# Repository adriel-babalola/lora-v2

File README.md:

# lora-v2

This is lora board version 2

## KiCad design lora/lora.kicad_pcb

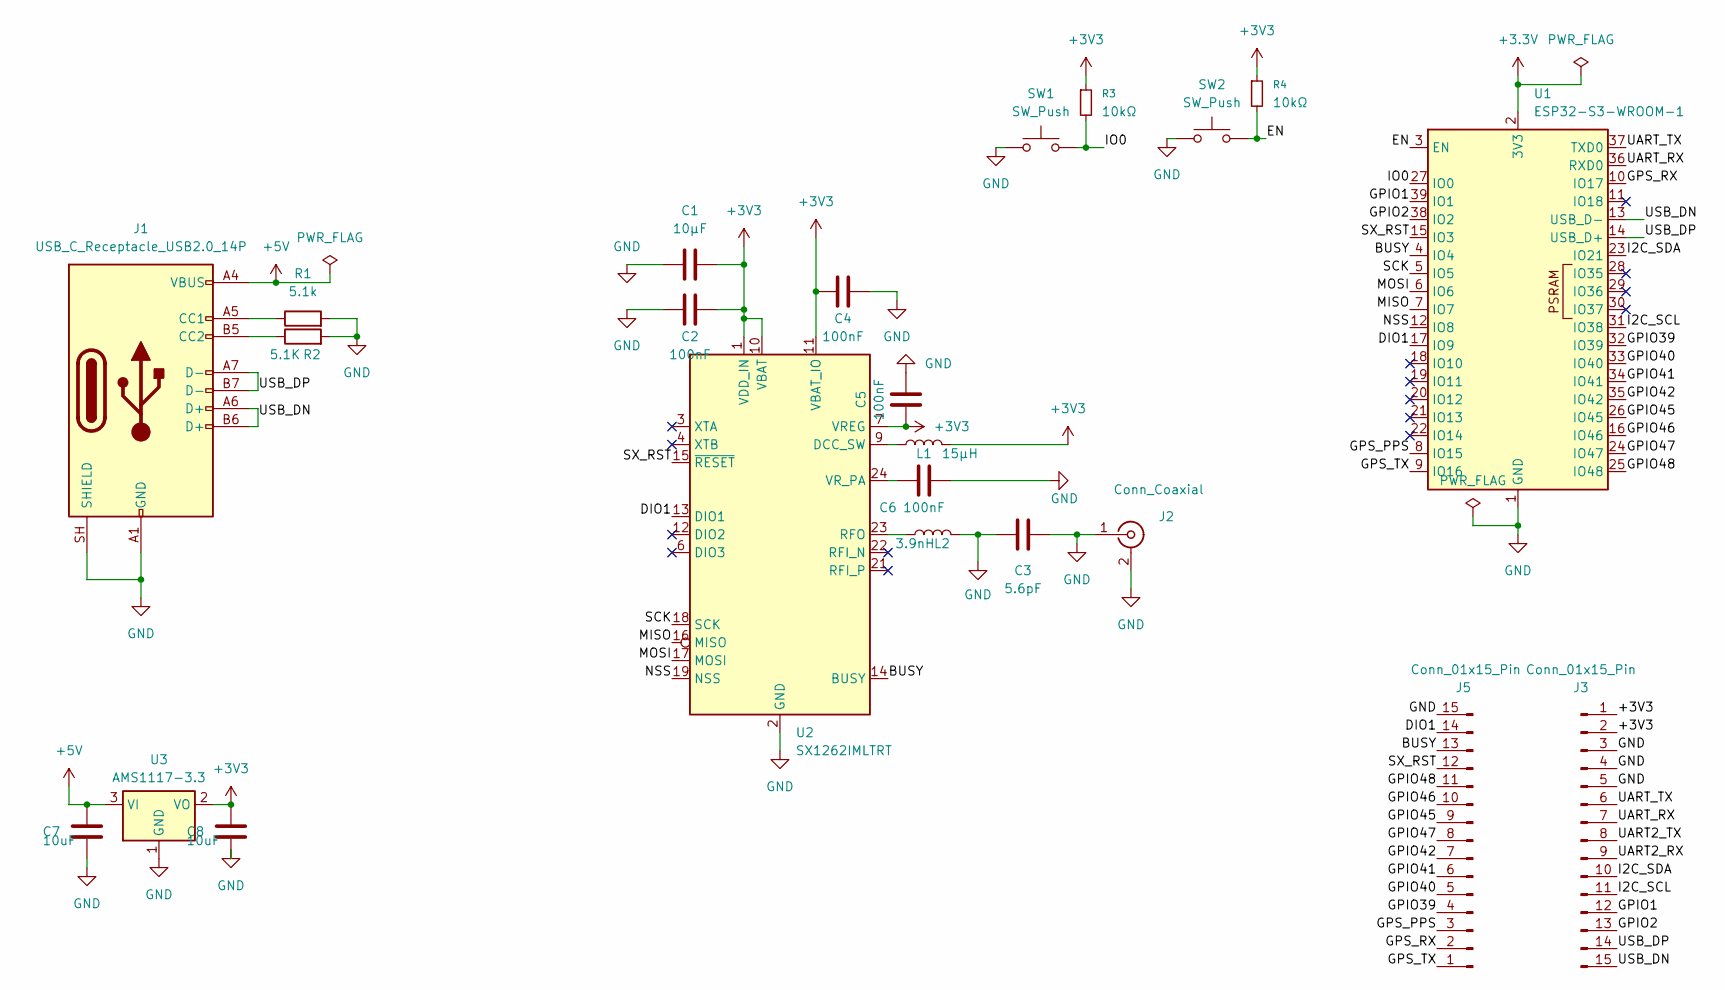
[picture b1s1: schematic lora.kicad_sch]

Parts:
C1: 10µF; C_0402_1005Metric
C2, C4, C5, C6: 100nF; C_0402_1005Metric
C3: 5.6pF; C_0402_1005Metric
C7, C8: 10uF; C_0402_1005Metric
J1: USB_C_Receptacle_USB2.0_14P; USB_C_Receptacle_HRO_TYPE-C-31-M-12
J2: Conn_Coaxial; U.FL_Hirose_U.FL-R-SMT-1_Vertical
J3, J5: Conn_01x15_Pin; PinHeader_1x15_P2.54mm_Vertical
L1: 15µH; L_0805_2012Metric
L2: 3.9nH; L_0402_1005Metric
R1: 5.1k; R_0402_1005Metric
R2: 5.1K; R_0402_1005Metric
R3, R4: 10kΩ; R_0402_1005Metric
SW1, SW2: SW_Push; SW_SPST_PTS645Sx43SMTR92
U1: ESP32-S3-WROOM-1
U2: SX1262IMLTRT; QFN-24-1EP_4x4mm_P0.5mm_EP2.6x2.6mm
U3: AMS1117-3.3; SOT-223-3_TabPin2

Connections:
+3.3V: U1.2 (3V3)
+3V3: C1.2, C2.2, C4.1, C5.1, C8.1, J3.1, J3.2, L1.2, R3.1, R4.1, U2.1 (VDD_IN), U2.7 (VREG), U2.10 (VBAT), U2.11 (VBAT_IO), U3.2 (VO)
+5V: C7.1, J1.A4 (VBUS), J1.A9 (VBUS), J1.B4 (VBUS), J1.B9 (VBUS), U3.3 (VI)
/BUSY: J5.13, U1.4 (IO4), U2.14 (BUSY)
/DIO1: J5.14, U1.17 (IO9), U2.13 (DIO1)
/EN: R4.2, SW2.2, U1.3 (EN)
/GPIO1: J3.12, U1.39 (IO1)
/GPIO2: J3.13, U1.38 (IO2)
/GPIO39: J5.4, U1.32 (IO39)
/GPIO40: J5.5, U1.33 (IO40)
/GPIO41: J5.6, U1.34 (IO41)
/GPIO42: J5.7, U1.35 (IO42)
/GPIO45: J5.9, U1.26 (IO45)
/GPIO46: J5.10, U1.16 (IO46)
/GPIO47: J5.8, U1.24 (IO47)
/GPIO48: J5.11, U1.25 (IO48)
/GPS_PPS: J5.3, U1.8 (IO15)
/GPS_RX: J5.2, U1.10 (IO17)
/GPS_TX: J5.1, U1.9 (IO16)
/I2C_SCL: J3.11, U1.31 (IO38)
/I2C_SDA: J3.10, U1.23 (IO21)
/IO0: R3.2, SW1.2, U1.27 (IO0)
/MISO: U1.7 (IO7), U2.16 (MISO)
/MOSI: U1.6 (IO6), U2.17 (MOSI)
/NSS: U1.12 (IO8), U2.19 (NSS)
/SCK: U1.5 (IO5), U2.18 (SCK)
/SX_RST: J5.12, U1.15 (IO3), U2.15 (~RESET)
/UART2_RX: J3.9
/UART2_TX: J3.8
/UART_RX: J3.7, U1.36 (RXD0)
/UART_TX: J3.6, U1.37 (TXD0)
/USB_DN: J1.A6 (D+), J1.B6 (D+), J3.15, U1.13 (USB_D-)
/USB_DP: J1.A7 (D-), J1.B7 (D-), J3.14, U1.14 (USB_D+)
GND: C1.1, C2.1, C3.1, C3.2, C4.2, C5.2, C6.1, C7.2, C8.2, J1.A1 (GND), J1.A12 (GND), J1.B1 (GND), J1.B12 (GND), J1.SH (SHIELD), J2.1 (In), J2.2 (Ext), J3.3, J3.4, J3.5, J5.15, L2.2, R1.2, R2.2, SW1.1, SW2.1, U1.1 (GND), U1.40 (GND), U1.41 (GND), U2.2 (GND), U2.5 (GND), U2.8 (GND), U2.20 (GND), U2.25 (GND), U3.1 (GND)
unnamed: J1.A5 (CC1), R1.1
unnamed: J1.B5 (CC2), R2.1
unnamed: L1.1, U2.9 (DCC_SW)
unnamed: L2.1, U2.23 (RFO)
unnamed: C6.2, U2.24 (VR_PA)

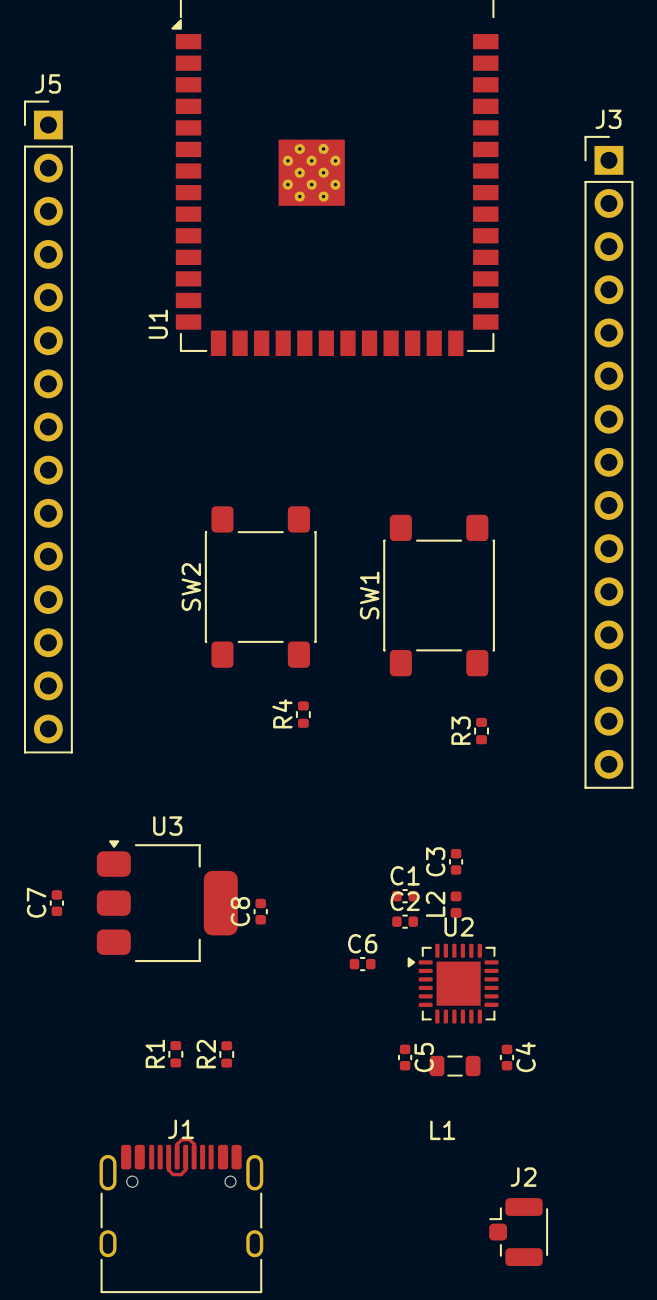
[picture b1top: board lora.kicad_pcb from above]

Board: 2 copper layers, 23 parts (0 on the bottom side), 36 nets.

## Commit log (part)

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2026-05-30 testing
